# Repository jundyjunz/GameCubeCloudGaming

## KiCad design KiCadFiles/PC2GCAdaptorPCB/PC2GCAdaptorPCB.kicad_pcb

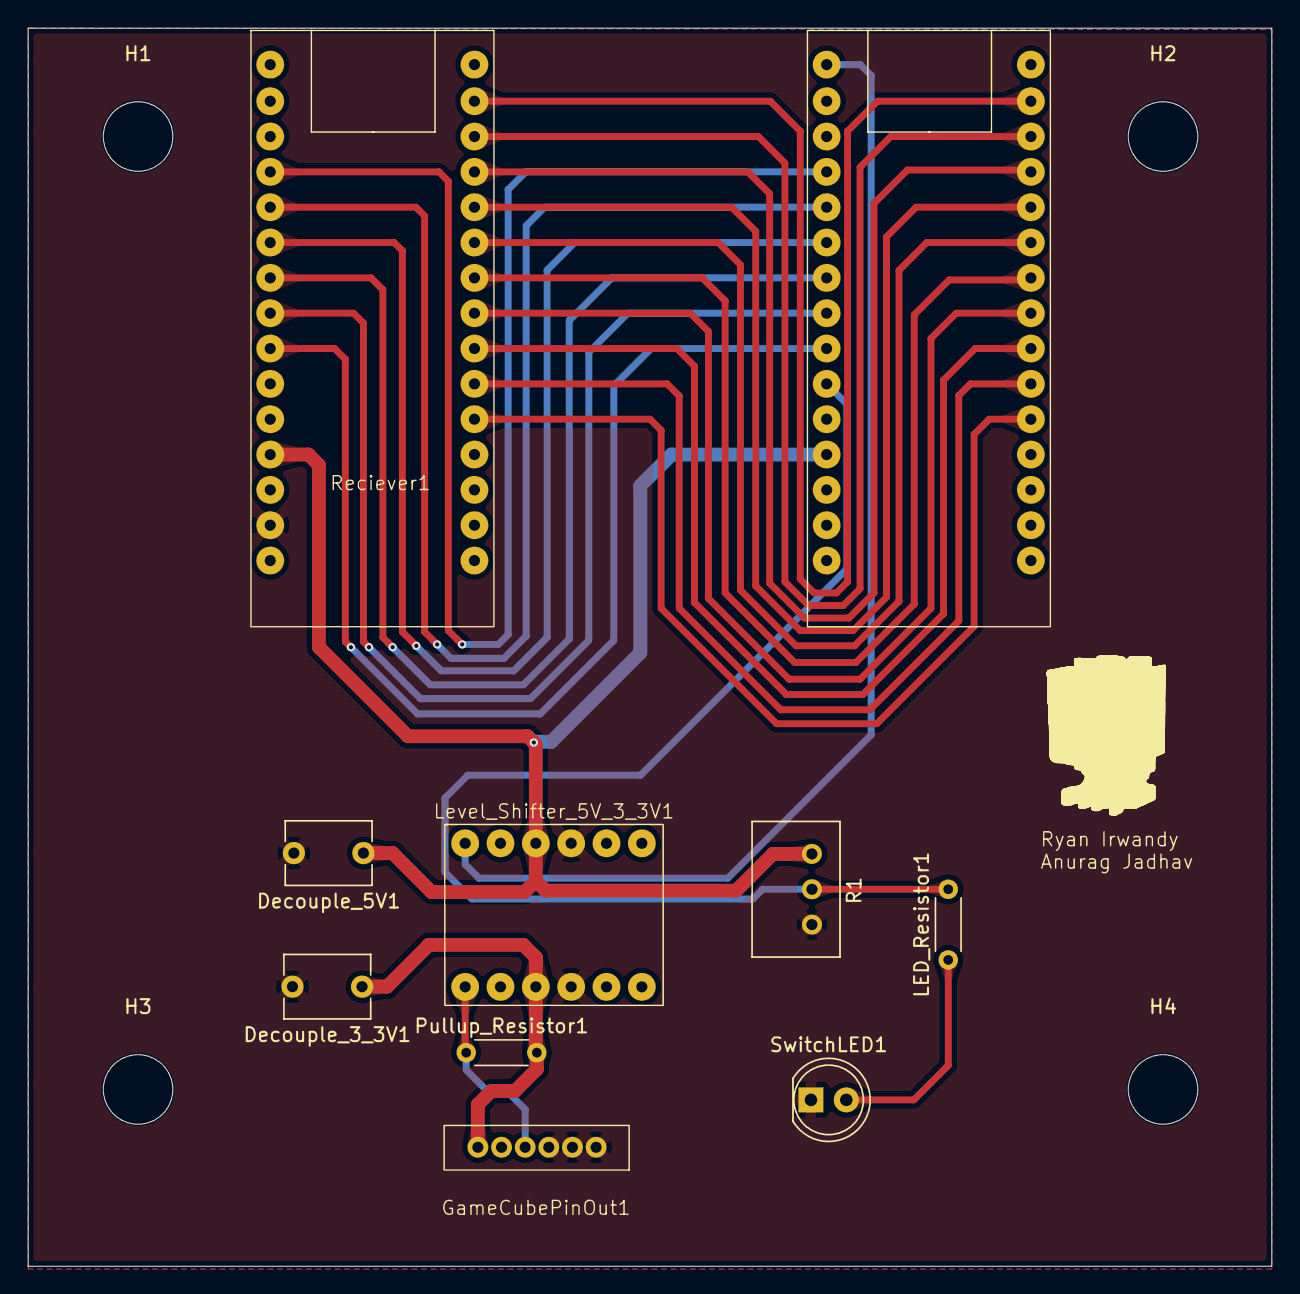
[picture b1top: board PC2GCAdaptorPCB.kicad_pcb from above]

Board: 2 copper layers, 89.4 x 89.0 mm, 14 parts (0 on the bottom side), 23 nets.

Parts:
Decouple_3_3V1, Decouple_5V1: 0.1nF; C_Disc_D6.0mm_W4.4mm_P5.00mm
GameCubePinOut1: GameCubePinOut
H1, H2, H3, H4: MountingHole; MountingHole_5mm
LED_Resistor1: 1K; R_Axial_DIN0204_L3.6mm_D1.6mm_P5.08mm_Horizontal
Level_Shifter_5V_3_3V1: LevelShifter
Pullup_Resistor1: 1k; R_Axial_DIN0204_L3.6mm_D1.6mm_P5.08mm_Horizontal
R1: Potentiometer; Potentiometer_Bourns_3299W_Vertical
Reciever1: Arduino_Nano
SwitchLED1: LED; LED_D5.0mm
Transmitter1: Arduino_Nano

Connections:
3.3V: Decouple_3_3V1.1, GameCubePinOut1.0 (Blue), Level_Shifter_5V_3_3V1.8 (LV), Pullup_Resistor1.2
5V: Decouple_5V1.1, Level_Shifter_5V_3_3V1.2 (HV), R1.3, Reciever1.26 (5V), Transmitter1.26 (5V)
A0: Reciever1.18 (A0), Transmitter1.18 (A0)
A1: Reciever1.19 (A1), Transmitter1.19 (A1)
A2: Reciever1.20 (A2), Transmitter1.20 (A2)
A3: Reciever1.21 (A3), Transmitter1.21 (A3)
A4: Reciever1.22 (A4), Transmitter1.22 (A4)
A5: Reciever1.23 (A5), Transmitter1.23 (A5)
D2: Reciever1.4 (D2), Transmitter1.4 (D2)
D3: Reciever1.5 (D3), Transmitter1.5 (D3)
D4: Reciever1.6 (D4), Transmitter1.6 (D4)
D5: Reciever1.7 (D5), Transmitter1.7 (D5)
D6: Reciever1.8 (D6), Transmitter1.8 (D6)
D7: Reciever1.9 (D7), Transmitter1.9 (D7)
D8: Reciever1.10 (D8), Transmitter1.10 (D8)
D9: Reciever1.11 (D9), Transmitter1.11 (D9)
D10: Reciever1.12 (D10), Transmitter1.12 (D10)
D11: Reciever1.13 (D11), Transmitter1.13 (D11)
Data_In: Level_Shifter_5V_3_3V1.0 (HV1), Transmitter1.15 (D13)
Data_Out: GameCubePinOut1.2 (Red), Level_Shifter_5V_3_3V1.6 (LV1), Pullup_Resistor1.1
GND: Decouple_3_3V1.2, Decouple_5V1.2, GameCubePinOut1.3 (Green), GameCubePinOut1.4 (White), GameCubePinOut1.5 (Black), Level_Shifter_5V_3_3V1.3 (GND), Level_Shifter_5V_3_3V1.9 (GND), R1.1, Reciever1.28 (GND), SwitchLED1.1 (K), Transmitter1.28 (GND)
unnamed: LED_Resistor1.1, SwitchLED1.2 (A)
unnamed: LED_Resistor1.2, R1.2, Transmitter1.24 (A6)

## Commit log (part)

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2026-02-27 websocketting stuff
2026-02-27 post version
2026-02-27 bug fixes
2026-03-05 moved from queues to circular buffers, and now producers contain one circular buffer from which the clients peek. No more buffer per client. they are also now stored as numpy arrays to prevent copyin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
2026-03-05 fixing l and r button
2026-03-06 multiprocessing here does not work
2026-03-06 stabilized arduino writes by removing double async speed
2026-03-06 removing some dependencies
2026-03-14 fixing controller connection and volume control frontend
2026-03-18 supports up to 7 clients on a good day
2026-03-19 supports up to rate limited audio and video capture in asyncio event loop which made faster writes to the arduino
2026-04-04 added switch for cstick and dpad control
2026-04-30 c# server implementation complete
2026-05-10 fixed bugs for multi adapter play.
    1. Fixed packetsingleton, originally stored data for one packet, now stores multiple packets when constructed, and will set up a seperate websocket for each when the correct multitoggle is enabled an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
    2. Fixed controlButtonCollection to reset the setKeyButtonListener() function by re improrting/resetting the button schemes. (setKeyButtonListener used to just take the first packet and cache it. now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
    3. fixed issue where now there is a delay between the read and write of 0xfa when connecting to an adapter for the first time.
    4. Miscellaneous: setting the packetsingleton now takes in a paacket type instead of a packet
2026-05-11 changed packet singleton back to almost original implementation. The original bug was me adding the extra number at the end of the route but it worked fine otherwise. no opdating cached buttons, or a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
2026-05-15 added support for multiple people on a single controller.
2026-05-19 completed page lock
2026-05-26 filepath fixes for linux
2026-05-27 Fixed left trigger right trigger bug, analog value also needs to be set to 255
2026-06-02 uploading sound detecting script
2026-06-02 push
2026-06-02 adding build for linux
2026-06-03 removed gamecube packet
2026-06-05 correct hardware name
2026-06-09 added timeout for issue when client unexpectedly disconnects.
2026-06-10 port switch, and added explanation as to why you cannot simply just reset the client specific command after each coalesce.
2026-06-12 Reducing memeory allocations, relieveing GC pressure, and disabling certain jpeg optimizations for easier processing.
2026-06-24 added option to buffer controller input for better less lag on older cpus
2026-06-28 adding more framerate adjustment features
